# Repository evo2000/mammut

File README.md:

# mammut

Clone of a silicon fuzz pedal. Effect PCB and footswitch PCB designed to be constructed in a Hammond 1590BB metal enclosure.

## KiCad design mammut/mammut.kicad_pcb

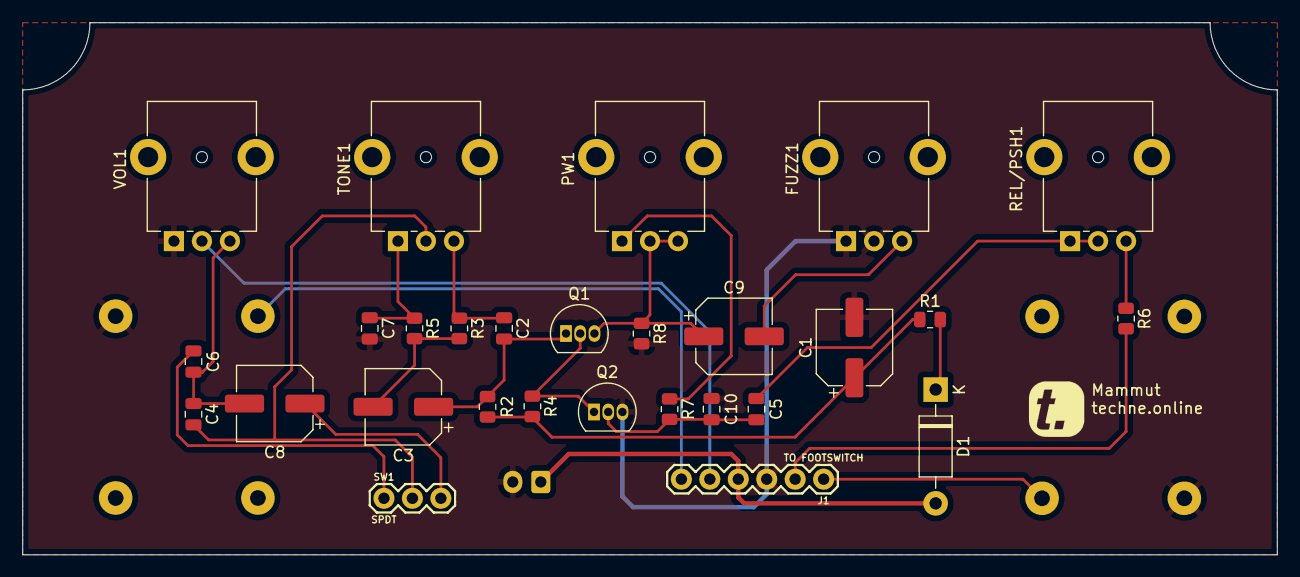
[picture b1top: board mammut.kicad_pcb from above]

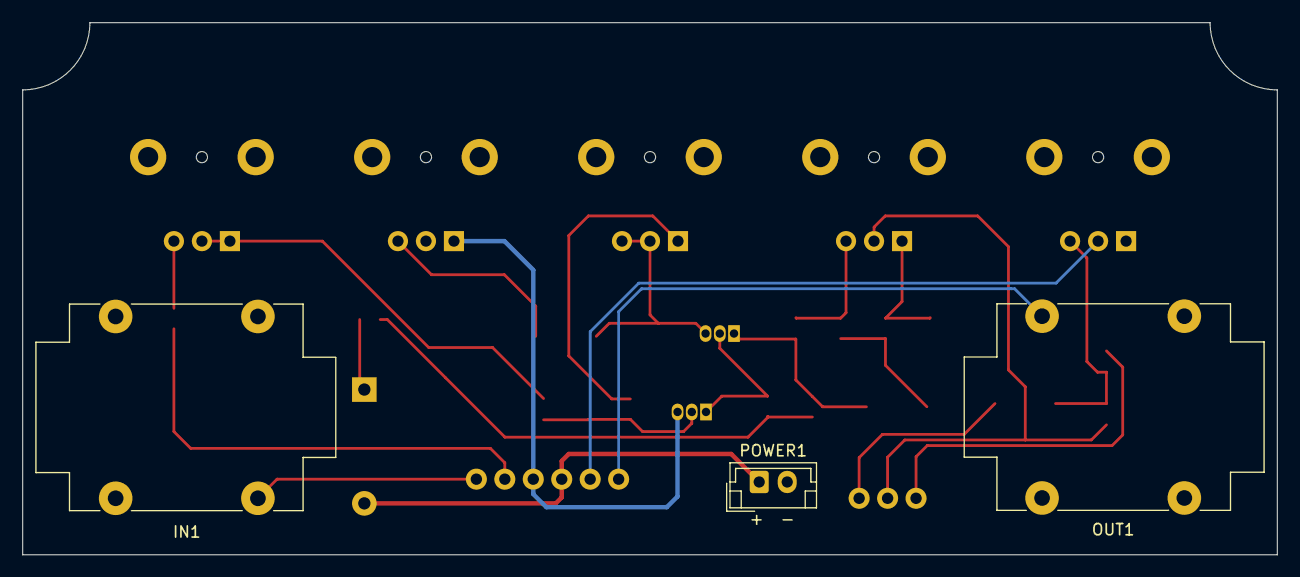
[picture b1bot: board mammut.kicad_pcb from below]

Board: 2 copper layers, 112.0 x 47.5 mm, 31 parts (3 on the bottom side), 23 nets.

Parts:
C1, C3, C8, C9: 100uF; CP_Elec_6.3x7.7
C2, C10: 10nF; C_0805_2012Metric
C4: 33nF; C_0805_2012Metric
C5, C7: 220nF; C_0805_2012Metric
C6: 68nF; C_0805_2012Metric
D1: 1N4007; D_DO-41_SOD81_P10.16mm_Horizontal
FUZZ1: C5K; Potentiometer_Alpha_RD901F-40-00D_Single_Vertical_CircularH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
IN1: IN; Jack_6.35mm_Neutrik_NMJ4HCD2_Horizontal
J1: TO FOOTSWITCH; 1X06
OUT1: OUT; Jack_6.35mm_Neutrik_NMJ4HCD2_Horizontal
POWER1: POWER; JST_EH_B2B-EH-A_1x02_P2.50mm_Vertical
PW1: B500K; Potentiometer_Alpha_RD901F-40-00D_Single_Vertical_CircularH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
Q1, Q2: TRANS_NPN-P2N2222A; TO-92L_Inline
R1, R6: 100; R_0805_2012Metric
R2: 22K; R_0805_2012Metric
R3: 10K; R_0805_2012Metric
R4: 56K; R_0805_2012Metric
R5: 5.1K; R_0805_2012Metric
R7: 100K; R_0805_2012Metric
R8: 2.2K; R_0805_2012Metric
REL/PSH1: B100K; Potentiometer_Alpha_RD901F-40-00D_Single_Vertical_CircularH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
SW1: SPDT; 1X03
TONE1: B10K; Potentiometer_Alpha_RD901F-40-00D_Single_Vertical_CircularH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
VOL1: B10K; Potentiometer_Alpha_RD901F-40-00D_Single_Vertical_CircularH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

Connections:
9V: D1.2, J1.4, POWER1.1
GND: C1.2, C7.2, C10.2, FUZZ1.1, FUZZ1.2, IN1.S, J1.3, OUT1.S, POWER1.2, Q2.3, R8.2, VOL1.1
IN: J1.2, R6.2
unnamed: C1.1, R1.1, R2.1, R4.2
unnamed: C2.1, R3.1, TONE1.3
unnamed: C2.2, C3.1, Q1.1, R2.2
unnamed: C3.2, R3.2, R5.2
unnamed: C4.1, C6.1, C8.2, VOL1.3
unnamed: C4.2, SW1.2, TONE1.2
unnamed: C5.2, REL/PSH1.1, REL/PSH1.2
unnamed: C6.2, SW1.1
unnamed: C7.1, R5.1, TONE1.1
unnamed: C8.1, SW1.3
unnamed: C9.1, PW1.2, PW1.3, Q1.3, R8.1
unnamed: C9.2, FUZZ1.3
unnamed: C5.1, C10.1, Q2.2, R7.2
unnamed: D1.1, R1.2
unnamed: IN1.T, J1.1
unnamed: J1.6, OUT1.T
unnamed: PW1.1, R7.1
unnamed: Q1.2, Q2.1, R4.1
unnamed: R6.1, REL/PSH1.3
OUT: J1.5, VOL1.2

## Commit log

2022-11-04 add kicad files
2022-11-04 add imgs
2023-01-12 prepare for plotting
